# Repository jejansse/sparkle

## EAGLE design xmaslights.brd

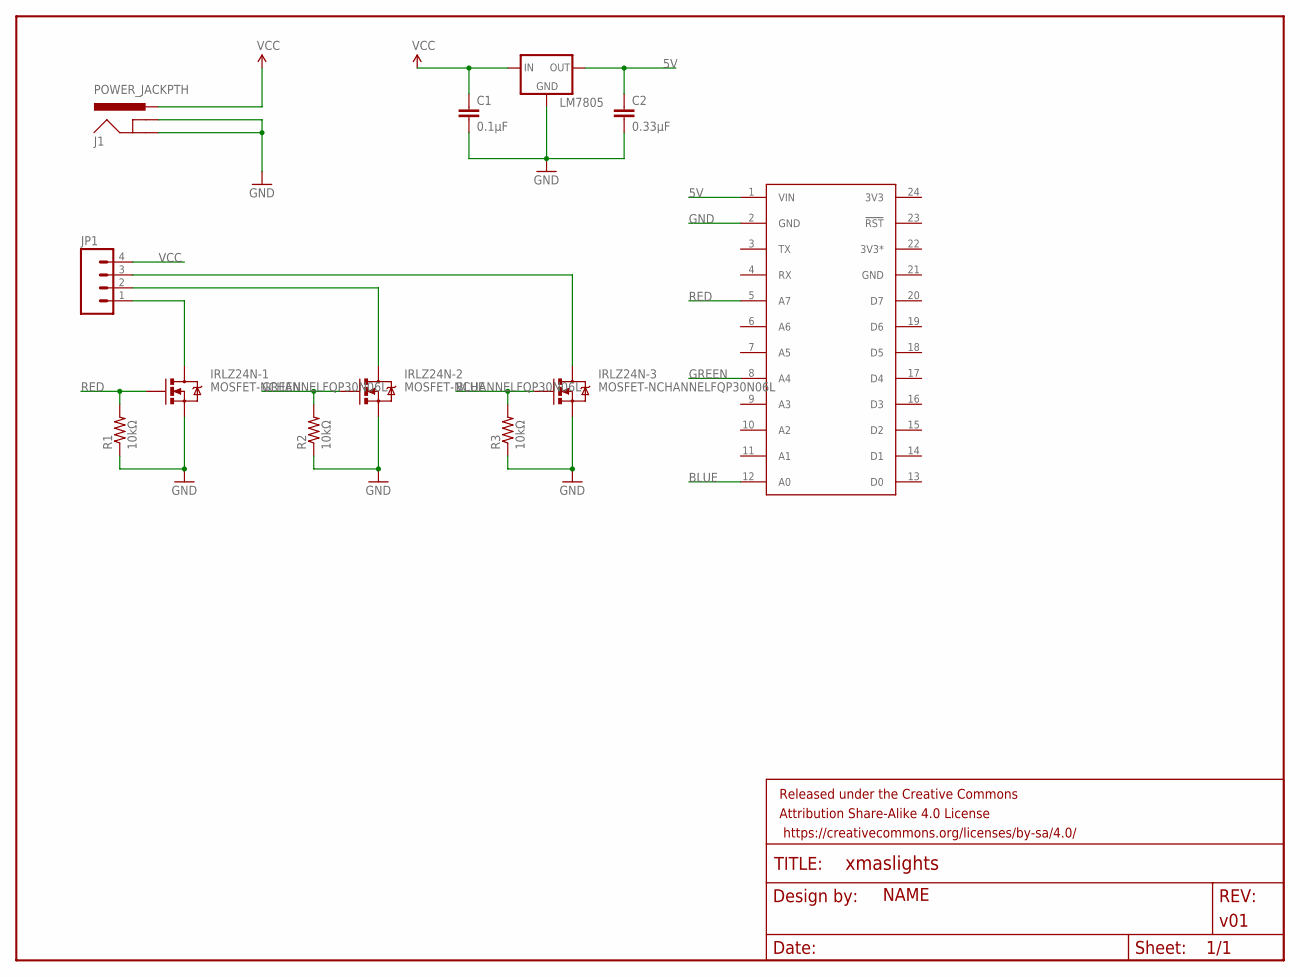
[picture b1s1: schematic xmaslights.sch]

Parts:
C1: 0.1µF; CAP-PTH-SMALL
C2: 0.33µF; CAP-PTH-SMALL
FRAME1: FRAME-LETTER; CREATIVE_COMMONS
IRLZ24N-1, IRLZ24N-2, IRLZ24N-3: MOSFET-NCHANNELFQP30N06L; TO220V
J1: POWER_JACKPTH; POWER_JACK_PTH
JP1: M04PTH; 1X04
LM7805: V_REG_78XXSINK; TO220-IGO
R1, R2, R3: 10kΩ; AXIAL-0.4
U$1: SPARK_CORECORE; SPARK_CORE

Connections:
3V3: U$1.24 (3V3)
3V3*: U$1.22 (3V3*)
5V: C2.1, LM7805.OUT, U$1.1 (VIN)
BLUE: IRLZ24N-3.1 (G), R3.P$2 (2), U$1.12 (A0)
GND: C1.2, C2.2, IRLZ24N-1.3 (S), IRLZ24N-2.3 (S), IRLZ24N-3.3 (S), J1.GND, J1.GNDBREAK, LM7805.GND, R1.P$1 (1), R2.P$1 (1), R3.P$1 (1), U$1.2 (GND), U$1.21 (GND)
GREEN: IRLZ24N-2.1 (G), R2.P$2 (2), U$1.8 (A4)
unnamed: IRLZ24N-1.2 (D), JP1.1
unnamed: IRLZ24N-2.2 (D), JP1.2
unnamed: IRLZ24N-3.2 (D), JP1.3
RED: IRLZ24N-1.1 (G), R1.P$2 (2), U$1.5 (A7)
VCC: C1.1, J1.PWR, JP1.4, LM7805.IN

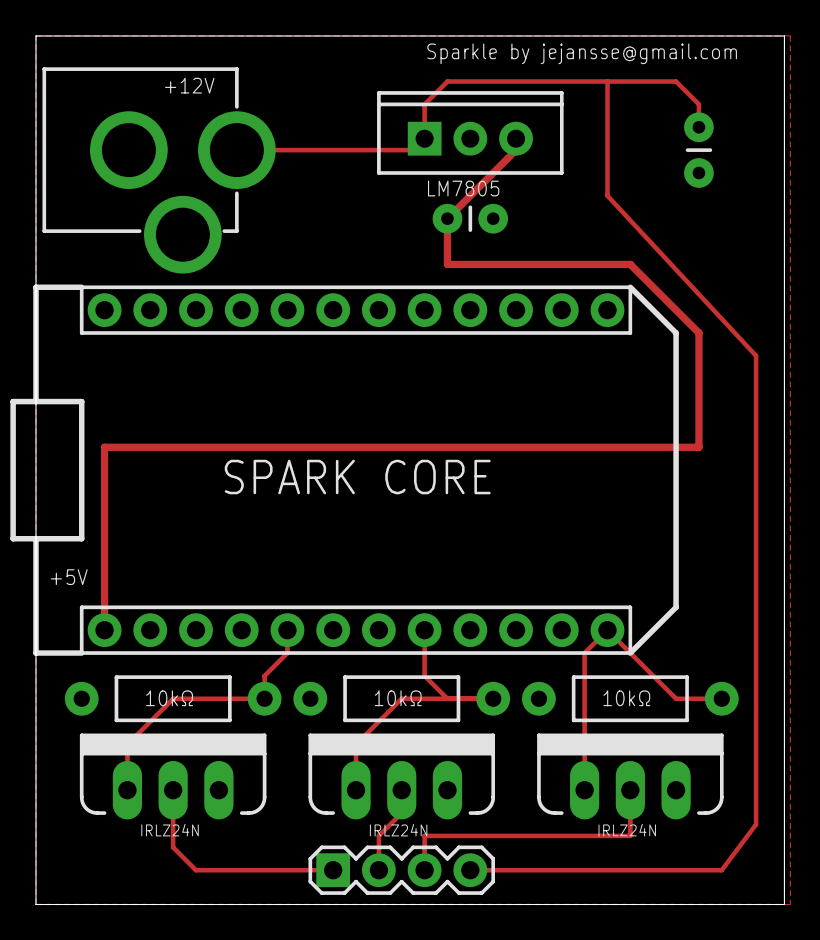
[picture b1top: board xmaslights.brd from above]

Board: 2 copper layers, 41.6 x 48.2 mm, 13 parts (0 on the bottom side), 9 nets.

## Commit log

2015-01-15 Add name + improve legibility of silkscreen

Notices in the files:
parts and their libraries:
SparkFun-Capacitors: Licensing: Creative Commons ShareAlike 4.0 International - https://creativecommons.org/licenses/by-sa/4.0
SparkFun-Aesthetics: Released under the Creative Commons Attribution Share-Alike 4.0 License
SparkFun-Aesthetics: https://creativecommons.org/licenses/by-sa/4.0
